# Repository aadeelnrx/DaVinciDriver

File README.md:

# DaVinciDriver

DaVinciDriver is an autonomous slotcar, scale 1:32

It is based on:
* Scalextric chassis W8835 Mercedes CLK (spare part for the Challenger)
* [Teensy 3.1](http://pjrc.com/teensy/teensy31.html)
* [Bosch BNO055 IMU](http://www.bosch-sensortec.com/en/homepage/products_3/sensor_hubs/iot_solutions/bno055_1/bno055_4), [Datasheet](http://ae-bst.resource.bosch.com/media/products/dokumente/bno055/BST_BNO055_DS000_12~1.pdf), on [Adafruit breakout board](https://learn.adafruit.com/adafruit-bno055-absolute-orientation-sensor/overview)
* [Toshiba TB6612FNG](http://toshiba.semicon-storage.com/info/docget.jsp?did=10660&prodName=TB6612FNG) H-bridge motor driver on [Pololu breakout board](https://www.pololu.com/product/713)
* [NRF24L01+](https://www.nordicsemi.com/kor/content/download/2726/34069/file/nRF24L01P_Product_Specification_1_0.pdf) radio link for telemetry and remote control
* VS1833 Infrared remote control

Libraries used:
* [dc740's library](https://forum.pjrc.com/threads/24307-nRF24L01-working-in-Teensy-2-0-and-Teensy-3-0) for NRF24L01:  [download](https://forum.pjrc.com/attachment.php?attachmentid=1002&d=1381184909)
* Adafruit libraries for BNO055: [download](https://github.com/adafruit/Adafruit_BNO055/archive/master.zip) and [download](https://github.com/adafruit/Adafruit_Sensor/archive/master.zip) (you need both)
* Greiman's SdFat Library: [download](https://github.com/greiman/SdFat)

License: GPL v2.0

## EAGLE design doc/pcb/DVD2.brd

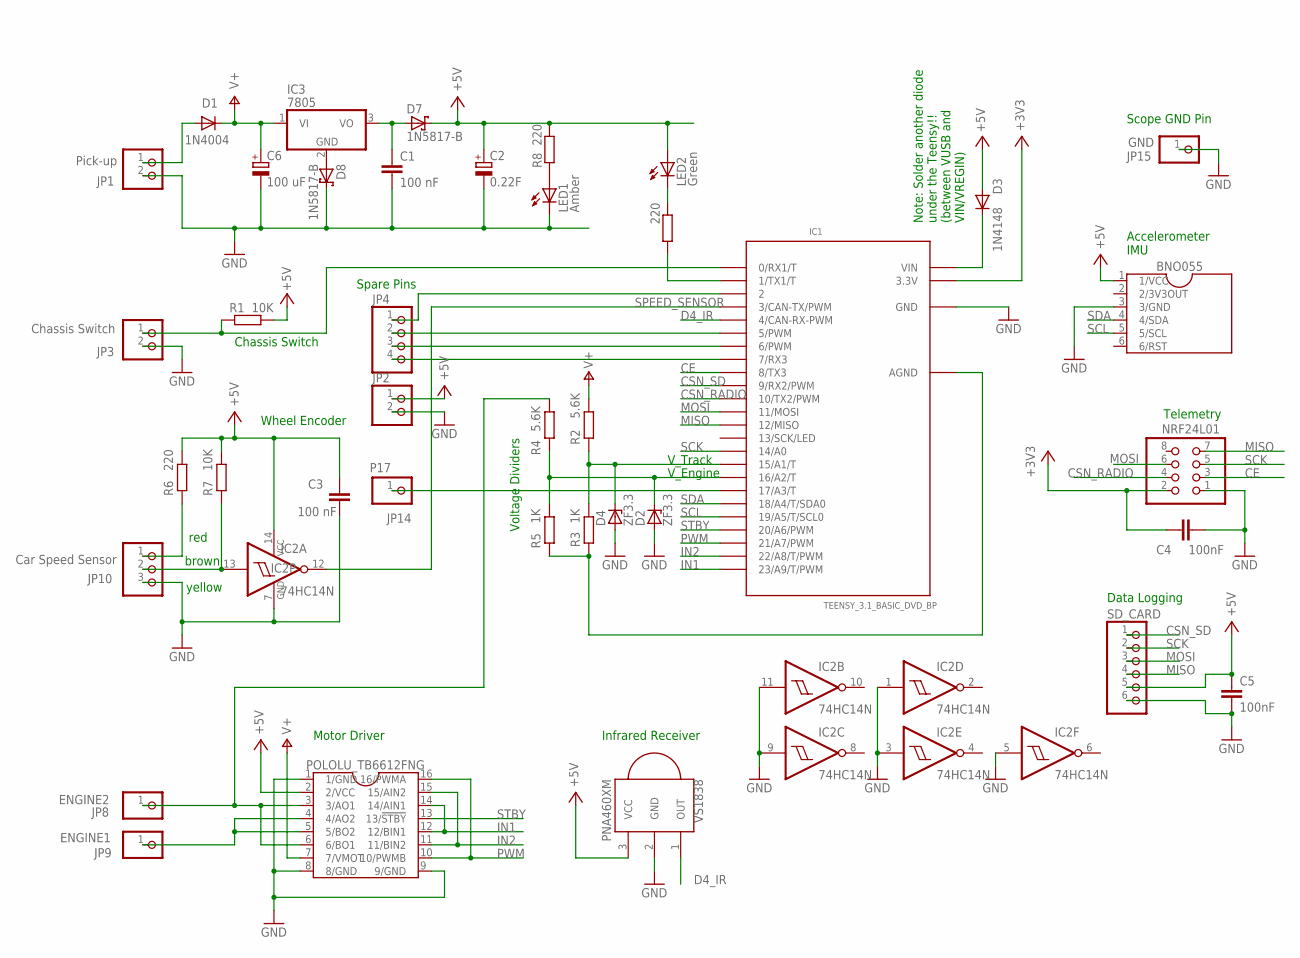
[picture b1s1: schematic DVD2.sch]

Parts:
BNO055: BNO055_LIGHT; DIL12-6-0
C1, C3: 100 nF; C025-025X050
C2: 0.22F; P128-50
C4: 100nF; C025-025X050
C5: 100nF; C025-024X044
C6: 100 uF; E2,5-6
D1: 1N4004; DO41-10
D2, D4: ZF3.3; ZDIO-7.5
D3: 1N4148; DO41-10
D7, D8: 1N5817-B; DO41-7.6
IC1: TEENSY_3.1_BASIC_DVD_BP; TEENSY_3.1_BASIC_DVD_BIGPADS
IC2: 74HC14N; DIL14
IC3: 7805; TO220V
IC4: POLOLU_TB6612FNG; DIL16WIDE
JP1: Pick-up; 1X02
JP2: PINHD-1X2; 1X02
JP3: Chassis Switch; 1X02
JP4: PINHD-1X4; 1X04
JP8: ENGINE2; 1X01
JP9: ENGINE1; 1X01
JP10: Car Speed Sensor; 1X03
JP14: P17; 1X01
JP15: GND; 1X01
LED1: Amber; LED3MM
LED2: Green; LED3MM
NRF24L01: PINHD-2X4; 2X04
R1, R7: 10K; 0207/10
R2, R4: 5.6K; 0207/10
R3, R5: 1K; 0207/10
R6, R8, R9: 220; 0207/10
SD_CARD: PINHD-1X6; 1X06
VS1838: PNA460XM

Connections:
2/3V3OUT: BNO055.2 (2/3V3OUT)
+3V3: C4.1, IC1.3.3V, NRF24L01.2
+5V: BNO055.1 (1/VCC), C2.+, C3.1, C5.1, D3.A, D7.C, IC2.14 (VCC), IC4.2 (2/VCC), JP2.1, LED2.A, R1.2, R6.2, R7.2, R8.2, SD_CARD.5, VS1838.3 (VCC)
AGND: IC1.AGND, R3.1, R5.1
CE: IC1.8 (8/TX3), NRF24L01.3
CSN_RADIO: IC1.10 (10/TX2/PWM), NRF24L01.4
CSN_SD: IC1.9 (9/RX2/PWM), SD_CARD.1
D4_IR: IC1.4 (4/CAN-RX-PWM), VS1838.1 (OUT)
ENGINE1: IC4.4 (4/AO2), IC4.5 (5/BO2), JP9.1
GND: BNO055.3 (3/GND), C1.2, C2.-, C3.2, C4.2, C5.2, C6.-, D2.A, D4.A, D8.C, IC1.GND, IC2.1 (I), IC2.3 (I), IC2.5 (I), IC2.7 (GND), IC2.9 (I), IC2.11 (I), IC4.1 (1/GND), IC4.8 (8/GND), IC4.9 (9/GND), JP1.2, JP2.2, JP3.2, JP10.3, JP15.1, LED1.K (C), NRF24L01.1, SD_CARD.6, VS1838.2 (GND)
IN1: IC1.23/A9 (23/A9/T/PWM), IC4.12 (12/BIN1), IC4.14 (14/AIN1)
IN2: IC1.22/A8 (22/A8/T/PWM), IC4.11 (11/BIN2), IC4.15 (15/AIN2)
JP8: IC4.3 (3/AO1), IC4.6 (6/BO1), JP8.1, R4.2
MISO: IC1.12 (12/MISO), NRF24L01.7, SD_CARD.4
MOSI: IC1.11 (11/MOSI), NRF24L01.6, SD_CARD.3
unnamed: D3.C, IC1.VIN
unnamed: JP10.1, R6.1
unnamed: IC1.5 (5/PWM), JP4.2
unnamed: LED2.K (C), R9.2
unnamed: C1.1, D7.A, IC3.3 (VO)
unnamed: IC1.17/A3 (17/A3/T), JP14.1
unnamed: LED1.A, R8.1
unnamed: D8.A, IC3.2 (GND)
unnamed: D4.C, IC1.15/A1 (15/A1/T), R2.1, R3.2
unnamed: D2.C, IC1.16/A2 (16/A2/T), R4.1, R5.2
unnamed: IC1.0 (0/RX1/T), JP3.1, R1.1
unnamed: IC1.1 (1/TX1/T), R9.1
unnamed: IC1.2, JP4.1
unnamed: IC1.6 (6/PWM), JP4.3
unnamed: IC1.7 (7/RX3), JP4.4
unnamed: IC2.13 (I), JP10.2, R7.1
PICKUP_PLUS: D1.A, JP1.1
PWM: IC1.21/A7 (21/A7/PWM), IC4.10 (10/PWMB), IC4.16 (16/PWMA)
SCK: IC1.14/A0, NRF24L01.5, SD_CARD.2
SCL: BNO055.5 (5/SCL), IC1.19/A5 (19/A5/T/SCL0)
SDA: BNO055.4 (4/SDA), IC1.18/A4 (18/A4/T/SDA0)
SPEED_SENSOR: IC1.3 (3/CAN-TX/PWM), IC2.12 (O)
STBY: IC1.20/A6 (20/A6/PWM), IC4.13 (13/!STBY)
V+: C6.+, D1.C, IC3.1 (VI), IC4.7 (7/VMOT), R2.2

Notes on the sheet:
Voltage Dividers
V_Track
V_Engine
Motor Driver
Wheel Encoder
Chassis Switch
Infrared Receiver
Accelerometer IMU
Telemetry
Data Logging
Note: Solder another diode under the Teensy!! (between VUSB and VIN/VREGIN)
Scope GND Pin
red
brown
yellow
Spare Pins

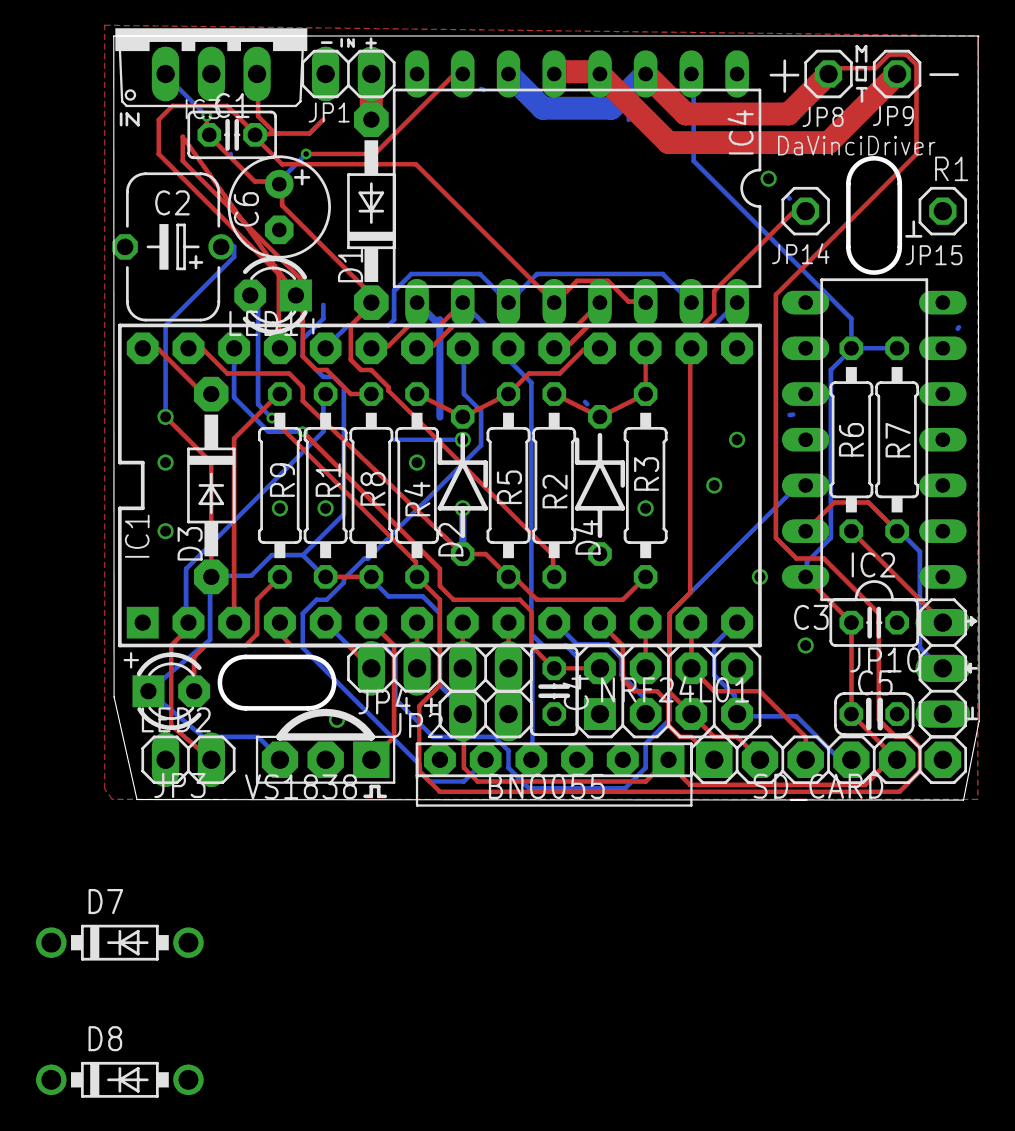
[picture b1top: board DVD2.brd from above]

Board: 2 copper layers, 48.1 x 42.5 mm, 40 parts (0 on the bottom side), 38 nets.

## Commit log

2015-08-07 Added License
2015-08-07 added source code to bring up the hardware
2015-08-08 added schematic and chassis scan
2015-08-08 Comment change
    Changed name DaVincoDriver to DaVinciDriver
2015-08-09 Adding IR Support
    Adding IR Support
2015-08-09 Modified IR switch
    Added translateIR and IR variables to IR_ON switch
2015-08-10 Added PCB first design
2015-08-10 Add .gitignore
2015-08-10 Added links to README file
2015-08-10 Cleanup and some first radio changes
    Radio is not working yet.
    - changed radio message struct to reflect the data types we have
    - move SPI's SCK pin to the one we use
    Cleanup:
    - renamed pin names to more uniform format
    - error() function now with "const" to fix a warning
2015-08-10 changed NRF24L01+ library in README
2015-08-10 Radio! It works now.
    The telemetry receiver runs on a second Teensy 3.1 that only
    has a NRF24L01+ on the same pins as the DaVinciDriver, but
    no other hardware.
2015-08-11 PCB Schematics update
    Added all known components
2015-08-11 PCB Board update
2015-08-12 Updated PCB
    Moved V+
    Added Capacitors
    Added power to schmitt trigger
2015-08-12 PCB Update
    Added connection from Pololu to voltage measuring resistors
2015-08-12 added TODO.txt
2015-08-12 Added PCB maximum outline
    The measurements are the inside of the chassis, i.e. the maximum
    PCB outline.
2015-08-14 Fixed wheel encoder for Teensy
2015-08-14 Added engine temperature measurement pin
2015-08-14 Added temperature, standby and engine voltage pins and variables
2015-08-15 Cleaned up parts of TODO list
    - declared STBY as ouput
    - added Diodes in Teensy input
    - ...
2015-08-15 Exchanged Teensy footprint PCB
2015-08-15 Fixed Pololu/BNO055/Teensy footprint
2015-08-16 Fixed DR violations & added Copper Pour GND
2015-08-16 PCB removed not connected pins from Teensy
2015-08-16 Created DVD.lbr for not existing parts and included them on PCB
2015-08-16 Cleanup of Telemetry receiver, indicate activity
    The LED goes on for 2 sec during setup() and then
    flashes every time a message was received.
    Also some cleanup.
2015-08-16 ignore local files
2015-08-16 PCB contacted Analog meas with AGND, removed temp meas
2015-08-16 Removed temp reading from Teensy Code
2015-08-16 Fixed small bug (endln)
2015-08-16 first autonomous drive
2015-08-16 Added one sided BNO055 to DVD.lbr
2015-08-16 added PID loop, increase LOG_INTEVAL
2015-08-17 Cleanup of Schematics
2015-08-17 Cleaned up eagle library symbols
2015-08-18 Updated schematic and added groundplate to board of PCB
2015-08-18 LED, caps, beauty
2015-08-19 PCB moved/added capacitors, changed voltage Pololu/BNO055, added pinouts & testpoints
    Only 1 testpoint connected
2015-08-19 Replaced axial by radial capacitor
2015-08-19 moved TPs, added Zener to ADC input
2015-08-19 Redid capacitor change
2015-08-19 bigger pads for Teensy
2015-08-20 measurements taken first in main loop
2015-08-20 Stop motor on error, code cleanup
    I introduced macros for logging to serial, SD-card,
    and both.
    This greatly simplifies and shortens the code.
    If you want to test the macros, copy their definitions
    to a test.c file, add some lines using the macros,
    and run gcc on it like this:
2015-08-23 Redrawn Chassis Picture, fixed schematic and created Board
    Please review and give comments
2015-08-24 Schematics and PCB Updates
    Schematics:
    - connected all unused gates of 7414 to GND because open
    inputs may draw a lot of current
    - renamed net for PickUp+ so that I can find it in the PCB
    - went through ERC
    PCB:
2015-08-25 PCB updates only
2015-08-26 PCB: new pads, ripup, partial route
2015-08-27 PCB routed
2015-08-29 PCB updates
    Moved voltage regulator
    Checked that the OKI switching regulator would also fit (it does)
    Moved capacitors around voltage regulator
    Moved motor pins but couldn't make one square
    Made other pin 1 square
    Added more vias to the ground copper pour
2015-08-29 PCB and Schematic Updates
    - Added 2-pin jumper for +5V and GND near the 4-pin header with
    spare signal pins
    - Added Langloecher
    - Cut the lower corners of the PCB to make it fit into the car
2015-08-30 Silkscreen cleanup, reconnected Vin to 7805
2015-08-30 Added Pictures of Prototype and Teensy diode
2015-08-31 Added Order List
2015-09-01 moved Langloecher to other layer and back
2015-09-23 Added IR Starting Light
    Defined Button PLAY/PAUSE as start/green light
2015-09-25 Updated IR Starting Lights with starting/stopping/blinking lights while waiting
    Defined:
    CH Lights on/off
    PLAY/PAUSE Race Start
    EQ Race Stop
2015-09-25 Fix IRStartingLight logic
2015-09-27 Added comments to IR codes
2015-10-15 Set STBY pin high for Pololu
2015-10-18 Boot time reduced, improved PID loop, radio link
    Booting time is reduced/improved by re-arranging
    the code and removing unnecessary delay() functions.
    The PID loop now updates with 100 Hz (was 10 Hz),
    while the measurement/logging loop is still at 10 Hz.
    This results in a much smoother drive, no pumping.
    PID parameters also tweaked a little.
2015-10-28 Changed SD card library to SdFat library
    downloaded from:
    https://github.com/greiman/SdFat
2015-11-19 Fixed DVD.lbr BNO055
    Fixed pin layout of BNO055
2015-11-19 Created V2 of DVD schematics
    Created V2 of DVD schematics with added diode after voltage regulator
    and fixed BNO055
2015-11-23 Added BNO055 switch
    Now it's possible to switch off BNO055
2015-12-01 Added Capacitor Report
2015-12-01 Added additional diode to voltage regulator GND connection
    Added diode to get the ref voltage correct
2015-12-06 Fixed SD Card storing of Data
    Fixed SD Card storing of Data
2015-12-06 Change PID SetSampleTime from fixed value to PID_INTERVAL value
2015-12-06 Adding Data to analyse
2015-12-07 Introduced Metro Timer reset
    - Introduced Metro Timer reset
    - put MOTOR_D = 0
    - Included LOGGER14.CSV
2015-12-07 Fixed logged Speed
    Added variable speedReadingLogged which is increased at speedReading and
    zeroed at logging
2015-12-07 Added pid_timer reset during logging to fix interval overlap
    - Added pid_timer reset during logging to fix interval overlap
    - added corresponding LOGGER16.CSV
2015-12-08 Pictures of different PID Measurements
2015-12-09 Added capture with 30ms and modified PID values
2015-12-16 Track Recognition & Curve Classification added
    Also measurement intervals put together to 30 ms
2015-12-18 Fixed Fault in stopping the car
2015-12-18 Added switches for amount of logging
2015-12-18 Modified PID/Logging interval to 10ms
    with reduced measuring/logging, the time needed is around 2-3ms =>
    PID/logging interval can be reduced to 10ms
2015-12-26 Measurements with real Driving and Acceleration/brake test
2015-12-30 send track details over radio
2015-12-31 initial checkin
2016-01-07 add more tests, cleanup
2016-01-07 Bugfix: motor_brake_coast() did not brake
2016-01-07 Added more tests, cleanup
2016-01-07 Added missing column header, fix outlier values
2016-01-07 many updates including not ready race mode
2016-01-10 Fixed direction reading
    Fixed the 360 => 0 and 0 => 360 direction problem
2016-01-13 Split file into several files
2016-01-16 Added lap consolidation
    Lap has been reduced to it's minimum speed area/maximum curve radius
2016-01-18 Extracted infrared code into its own file
2016-01-18 Only initialize and use BNO when Track Power is present
2016-01-18 Updated DVD2 with extra Diode(s)
2016-01-30 New variable to indicate if track power is present
2016-02-02 Move code from the main loop into functions
2016-02-14 Split the main file into several smaller files.
    Main Loop is now calling functions from measuring.cpp and racing.cpp.
2016-02-14 Simulator for the measuring functions.
    It reads the speed and direction from a previously recorded
    CSV file.
    I don't know if GIT stores symbolic links as links or if it
    copies the files.
    Here you can see which files are only links and which are not:
    -rw-r--r-- 1 alex alex2 4101 14 Feb 18:22 Arduino.cpp
2016-05-06 Modified BNO on check
    added text (no track voltage?)
    removed while(1), why was that there?????
